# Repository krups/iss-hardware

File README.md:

# Kentucky RE-entry Probe Experiment 2
Board files, schematics, DXF, BOM, partslist and documentation for the KREPE-2 mission, part of the KRUPS campaign at the University of Kentucky. Documentation PDF can be found [Flight Computer Hardware Manual](doc/krepe-flight-computer-manual.pdf).

Documentation for the KREPE-1 mission can be found on the krepe1 branch [here](https://github.com/krups/iss-hardware/blob/krepe1/doc/krepe-flight-computer-manual.pdf).

### Board renders

### Libraries and datasheets for components
- Thermocouple to digital converter
  -  [MAX31856 Library](https://github.com/adafruit/Adafruit_MAX31856)
  -  [MAX31856 Datasheet](https://datasheets.maximintegrated.com/en/ds/MAX31856.pdf)
- Analog Multiplexer
  - [ADG609BRUZ datasheet](https://www.analog.com/media/en/technical-documentation/data-sheets/ADG608_609.pdf)
- Debug Radio
  - [RFM69HCW](https://www.digikey.com/product-detail/en/sparkfun-electronics/COM-13909/1568-1394-ND/6023504)
- 9-axis IMU
  - [DPE Library](https://github.com/drcpattison/DPEng_ICM20948_AK09916)
  - [Sparkfun Library](https://github.com/sparkfun/SparkFun_ICM-20948_ArduinoLibrary)
  - [Datasheet](https://www.invensense.com/wp-content/uploads/2016/06/DS-000189-ICM-20948-v1.3.pdf)
- Solid state relay
  - [Datasheet](https://www.digikey.com/product-detail/en/panasonic-electric-works/AQV252GAX/255-3375-1-ND/2810282)
- High G Accelerometer
  - [Datasheet](https://www.digikey.com/product-detail/en/analog-devices-inc/ADXL377BCPZ-RL7/ADXL377BCPZ-RL7CT-ND/3678489)
- Safety Co-processor
  - [Datasheet](https://www.digikey.com/product-detail/en/microchip-technology/ATSAMD21E16B-MFT/ATSAMD21E16B-MFTCT-ND/5455793)
  - [Arduino variant reference](https://github.com/adafruit/ArduinoCore-samd/blob/master/variants/trinket_m0/variant.cpp)
 
### Teensy pin assignments wrt. to Arduino 

| Teensy Arduino Pin      | Net Name                 | Notes      |
|-------------------------|--------------------------|------------------|
| 0                       | CAPSENSE 1               |  input, read with ```touchRead(pin)```                |
| 1                       | CAPSENSE 0               |  input, read with ```touchRead(pin)```                |
| 3                       | LED IRIDIUM ON           |  active high                |
| 4                       | LED IRIDIUM SIGNAL_OK    |    active high              |
| 5                       | LED IRIDIUM TRANSMITTING |    active high              |
| 6                       | LED ISM TRANSMITTING     |    active high              |
| 7                       | LED ACTIVITY             |    active high              |
| 8			  | CS_DSP		     | active low chip select for DSP310 pressure sensor |
| 9                       | CS_ISM                   |    rfm69 chip select              |
| 11                      | MOSI                     |                  |
| 12                      | MISO                     |                  |
| 13                      | SCLK                     |                  |
| 14                      | BAT_STAT                 |    high when charging              |
| 15                      | CAPSENSE2                |     input, read with ```touchRead(pin)```             |
| 16                      | MUX0                     |    output to analog mux              |
| 17                      | MUX1                     |    output to analog mux              |
| 18                      | SDA                      |                  |
| 19                      | SCL                      |                  |
| 20                      | CS@TC1                   |  U12 chip select                |
| 21                      | CS@TC2                   |  U13 chip select                |
| A8                      | BAT SENSE                | (A8)  halved by voltage divider           |
| 23                      | PRI ACT                  | output to iridium activation 'AND' gate  |
| 24                      | BUZZER                   |     buzzer output             |
| 25                      | TC1 FAULT                | (ACTIVE LOW)     |
| 26                      | TC2 FAULT                | (ACTIVE LOW)     |
| 27                      | SEC CTRL 2               |       i/o to safety processor           |
| 28                      | RESET ISM                |  reset to rfm69                |
| 28                      | INT ISM                  |  interrupt from rfm69                |
| 30                      | CAPSENSE3                |  input, read with ```touchRead(pin)```                |
| 31                      | RIRI                     | (IRIDIUM OUTPUT) |
| 32                      | TIRI                     | (IRIDIUM INPUT)  |
| 33                      | RADIO OFF SIG            | pulled high when 3.3v to ism radio is present                 |
| 34                      | FSYNC                    | IMU sync signal (not necessary for functionality)            |
| 35                      | INT                      | IMU interrupt pin (not necessary for functionality)            |
| 36                      | XOUT                     | (A17)  high g accel output          |
| 37                      | YOUT                     | (A18)  high g accel output          |
| 38                      | ZOUT                     | (A19)  high g accel output          |
| 39                      | SEC CTRL 1               |   i/o to safety processor               |
| A21                     | IRIDIUM TX ACT           |     iridium output indicating the module is actively transmitting RF             |
| A22                     | IRIDIUM STATUS           |  iridium output indicating an SBD message has arrived                |

### Safety processor pin assignments wrt. to Arduino 

The last four pins for the safety processor will need to be added into the board variant file for the trinket m0 since only 5 pins are mapped to physical pads on the current m0 variant.cpp file (or we can make our own arduino board support package ;) )

```SEC CTRL 1``` and ```SEC CTRL 1``` are to be used to coordinate use of the SPI bus so that both the Teensy and safety processor do not drive bus lines to opposite logic levels.

| Safety Processor Arduino Pin|   Net Name                       |                 Note |
|-------------------------|--------------------------|------------------|
| 1                       | CS@TC1                   |    also connected to teensy GPIO              |
| 13                      | CS@TC2                   |    also connected to teensy GPIO              |
| 7                       | SEC ACT                  |     output to activation 'AND' gate             |
| 8                       | SEC CTRL 1               |  i/o with teensy                |
| 0                       | SEC CTRL 2               |  i/o with teensy                |
| PA14                    | TC1 FAULT                |         input        |
| PA15                    | TC2 FAULT                |    input            |
| PA17                    | MUX0                     |       need to use i/o with teensy to avoid collisions on SPI bus           |
| PA18                    | MUX1                     |        need to use i/o with teensy to avoid collisions on SPI bus         |

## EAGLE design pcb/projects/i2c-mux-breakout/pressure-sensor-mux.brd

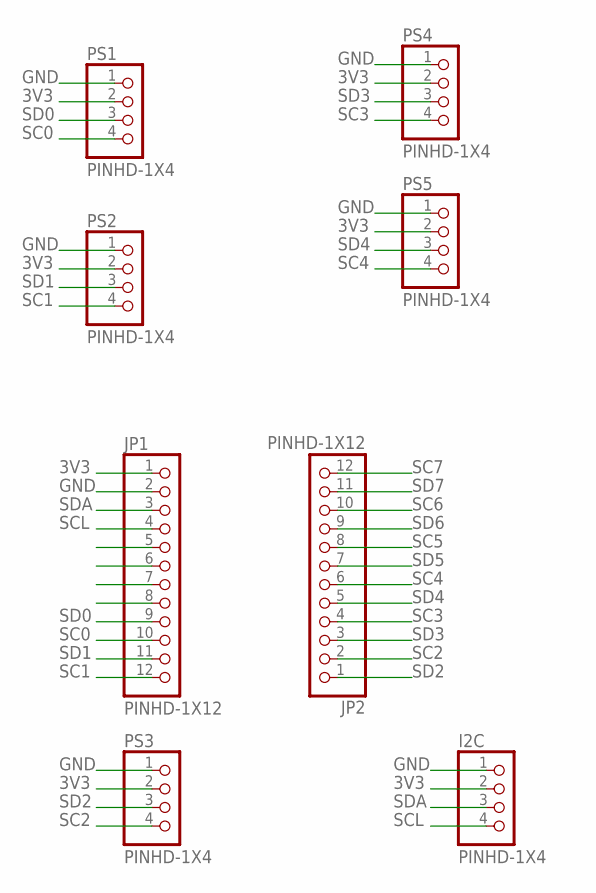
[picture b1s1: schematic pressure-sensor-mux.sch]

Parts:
I2C: PINHD-1X4; 1X04
JP1, JP2: PINHD-1X12; 1X12
PS1, PS2, PS3, PS4, PS5: PINHD-1X4; 1X04

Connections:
3V3: I2C.2, JP1.1, PS1.2, PS2.2, PS3.2, PS4.2, PS5.2
GND: I2C.1, JP1.2, PS1.1, PS2.1, PS3.1, PS4.1, PS5.1
SC0: JP1.10, PS1.4
SC1: JP1.12, PS2.4
SC2: JP2.2, PS3.4
SC3: JP2.4, PS4.4
SC4: JP2.6, PS5.4
SC5: JP2.8
SC6: JP2.10
SC7: JP2.12
SCL: I2C.4, JP1.4
SD0: JP1.9, PS1.3
SD1: JP1.11, PS2.3
SD2: JP2.1, PS3.3
SD3: JP2.3, PS4.3
SD4: JP2.5, PS5.3
SD5: JP2.7
SD6: JP2.9
SD7: JP2.11
SDA: I2C.3, JP1.3

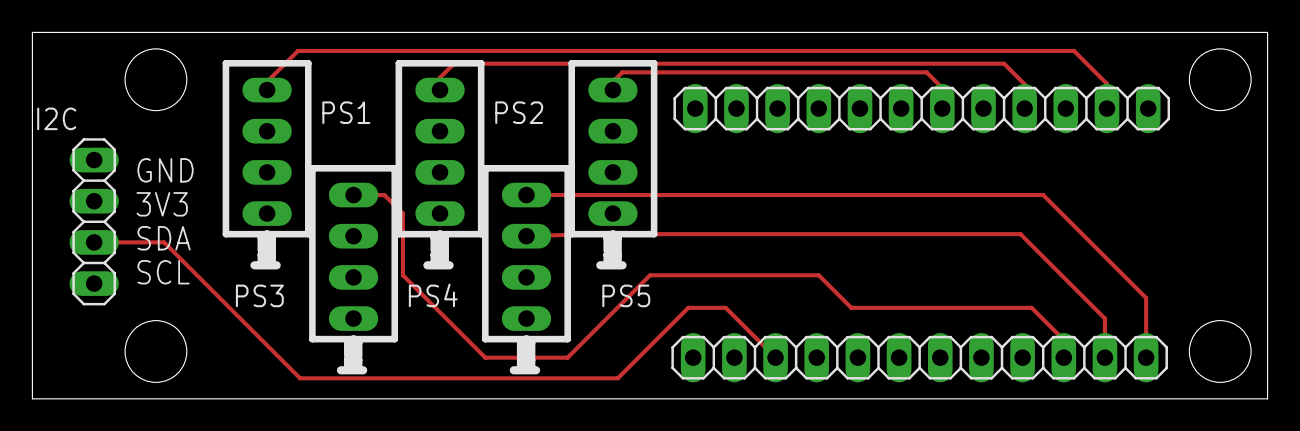
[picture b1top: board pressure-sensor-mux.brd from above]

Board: 4 copper layers, 76.2 x 22.6 mm, 8 parts (0 on the bottom side), 14 nets.

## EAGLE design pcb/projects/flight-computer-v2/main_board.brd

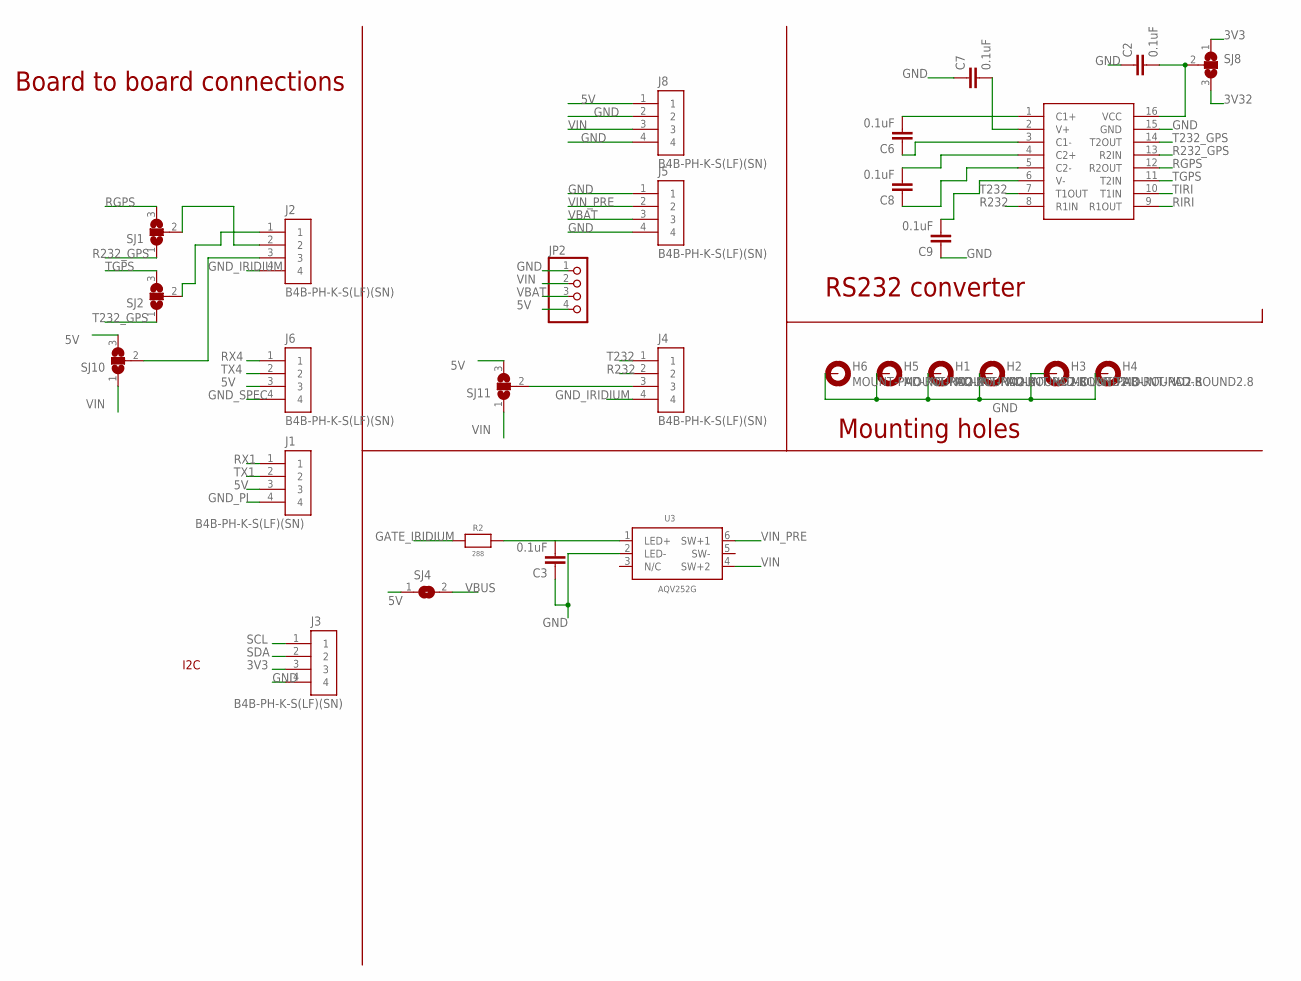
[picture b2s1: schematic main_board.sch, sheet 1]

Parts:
C2, C3, C6, C7, C8, C9: 0.1uF; C0603
H1, H2, H3, H4, H5, H6: MOUNT-PAD-ROUND2.8; 2,8-PAD
J1, J2, J3, J4, J5, J6, J8: B4B-PH-K-S(LF)(SN); JST_B4B-PH-K-S(LF)(SN)
JP2: PINHD-1X4; 1X04
R2: 288; 0603-NO
SJ1, SJ2, SJ8, SJ10, SJ11: SJ2W; SJ_2
SJ4: SJ
U3: AQV252G; SOP6
U11: UM3232EEAE; RQ_16_ADI

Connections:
3V3: J3.3, SJ8.1; also elsewhere on the board
3V32: SJ8.3; also elsewhere on the board
5V: J1.3, J6.3, J8.1, JP2.4, SJ4.1, SJ10.3, SJ11.3; also elsewhere on the board
GATE_IRIDIUM: R2.1; also elsewhere on the board
GND: C2.1, C3.1, C7.1, C9.1, H1.B2,8, H2.B2,8, H3.B2,8, H4.B2,8, H5.B2,8, H6.B2,8, J3.4, J5.1, J5.4, J8.2, J8.4, JP2.1, U3.2 (LED-), U11.15 (GND); also elsewhere on the board
GND_IRIDIUM: J2.4, J4.4
GND_PI: J1.4
GND_SPEC: J6.4
unnamed: J2.1, SJ2.2
unnamed: J2.2, SJ1.2
unnamed: C6.2, U11.1 (C1+)
unnamed: J2.3, SJ10.2
unnamed: C2.2, SJ8.2, U11.16 (VCC)
unnamed: C7.2, U11.2 (V+)
unnamed: C6.1, U11.3 (C1-)
unnamed: C8.2, U11.4 (C2+)
unnamed: C8.1, U11.5 (C2-)
unnamed: C9.2, U11.6 (V-)
unnamed: J4.3, SJ11.2
unnamed: C3.2, R2.2, U3.1 (LED+)
R232: J4.2, U11.8 (R1IN)
R232_GPS: SJ1.1, U11.13 (R2IN)
RGPS: SJ1.3, U11.12 (R2OUT); also elsewhere on the board
RIRI: U11.9 (R1OUT); also elsewhere on the board
RX1: J1.1; also elsewhere on the board
RX4: J6.1; also elsewhere on the board
SCL: J3.1; also elsewhere on the board
SDA: J3.2; also elsewhere on the board
T232: J4.1, U11.7 (T1OUT)
T232_GPS: SJ2.1, U11.14 (T2OUT)
TGPS: SJ2.3, U11.11 (T2IN); also elsewhere on the board
TIRI: U11.10 (T1IN); also elsewhere on the board
TX1: J1.2; also elsewhere on the board
TX4: J6.2; also elsewhere on the board
VBAT: J5.3, JP2.3; also elsewhere on the board
VBUS: SJ4.2; also elsewhere on the board
VIN: J8.3, JP2.2, SJ10.1, SJ11.1, U3.4 (SW+2)
VIN_PRE: J5.2, U3.6 (SW+1)

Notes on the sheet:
Board to board connections
I2C
RS232 converter
Mounting holes

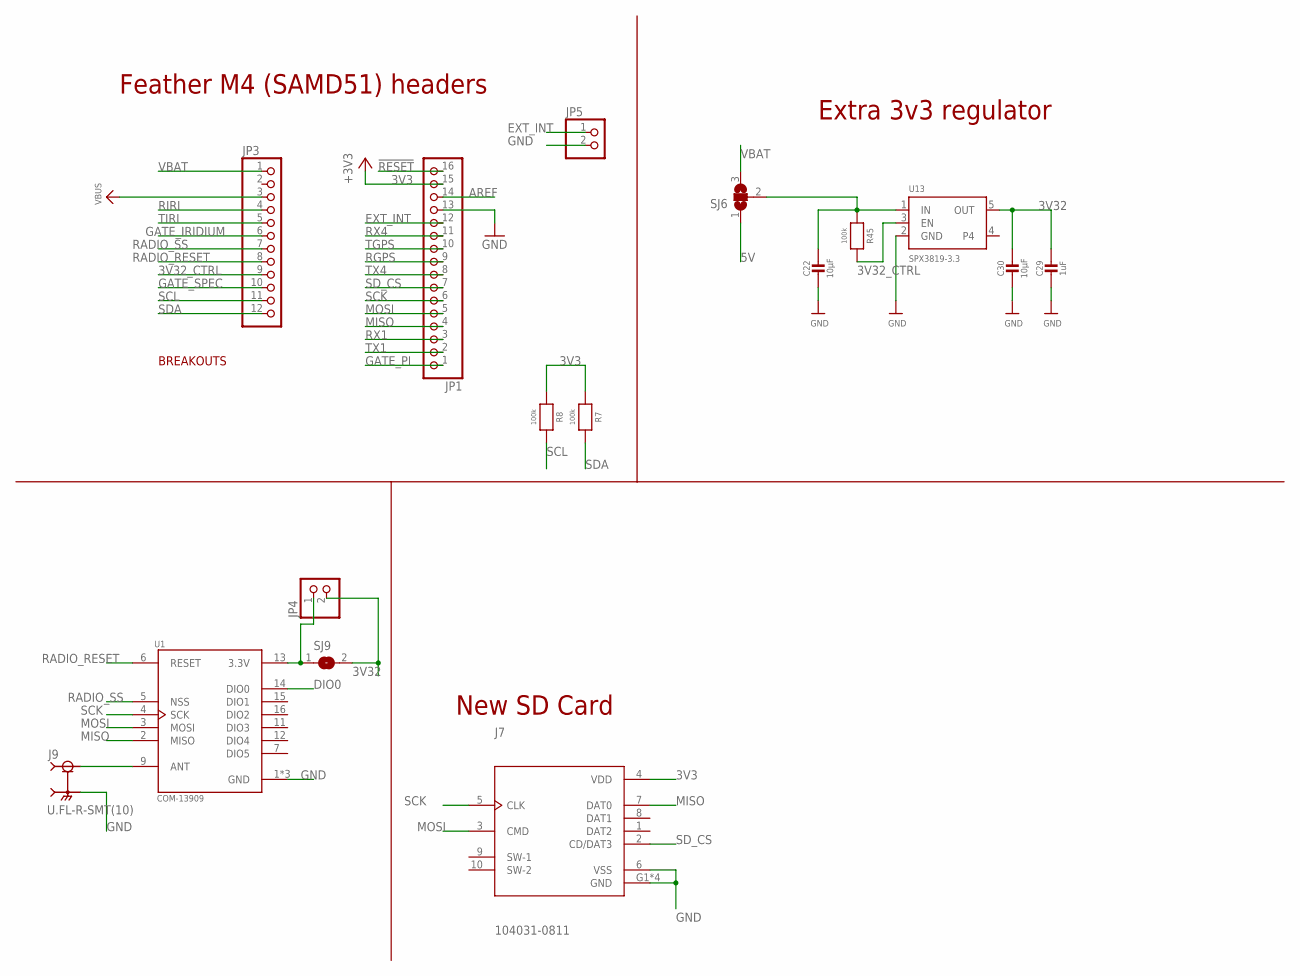
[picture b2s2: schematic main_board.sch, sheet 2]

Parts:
C22, C30: 10µF; 0805-NO
C29: 1uF; 0603-NO
J7: 104031-0811; MOLEX_104031-0811
J9: U.FL-R-SMT(10); HRS_U.FL-R-SMT(10)
JP1: HEADER-1X16ROUND; 1X16_ROUND
JP3: HEADER-1X12; 1X12_ROUND
JP4, JP5: PINHD-1X2; 1X02
R7, R8, R45: 100k; 0603-NO
SJ6: SJ2W; SJ_2
SJ9: SJ
U1: COM-13909; MOD_COM-13909
U13: SPX3819-3.3; SOT23-5

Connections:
3V3: J7.4 (VDD), JP1.15, R7.1, R8.1; also elsewhere on the board
3V32: C29.1, C30.1, JP4.2, SJ9.2, U13.5 (OUT); also elsewhere on the board
3V32_CTRL: JP3.9, R45.2, U13.3 (EN); also elsewhere on the board
5V: SJ6.1; also elsewhere on the board
!RESET: JP1.16
AREF: JP1.14
DIO0: U1.14 (DIO0)
EXT_INT: JP1.12, JP5.1
GATE_IRIDIUM: JP3.6; also elsewhere on the board
GATE_PI: JP1.1; also elsewhere on the board
GATE_SPEC: JP3.10; also elsewhere on the board
GND: C22.2, C29.2, C30.2, J7.6 (VSS), J7.G1 (GND), J7.G2 (GND), J7.G3 (GND), J7.G4 (GND), J9.2 (GND), J9.3 (GND), JP1.13, JP5.2, U1.1 (GND), U1.8 (GND), U1.10 (GND), U13.2 (GND); also elsewhere on the board
MISO: J7.7 (DAT0), JP1.4, U1.2 (MISO)
MOSI: J7.3 (CMD), JP1.5, U1.3 (MOSI)
unnamed: JP4.1, SJ9.1, U1.13 (3.3V)
unnamed: C22.1, R45.1, SJ6.2, U13.1 (IN)
unnamed: J9.1 (SIG), U1.9 (ANT)
RADIO_RESET: JP3.8, U1.6 (RESET)
RADIO_SS: JP3.7, U1.5 (NSS)
RGPS: JP1.9; also elsewhere on the board
RIRI: JP3.4; also elsewhere on the board
RX1: JP1.3; also elsewhere on the board
RX4: JP1.11; also elsewhere on the board
SCK: J7.5 (CLK), JP1.6, U1.4 (SCK)
SCL: JP3.11, R8.2; also elsewhere on the board
SDA: JP3.12, R7.2; also elsewhere on the board
SD_CS: J7.2 (CD/DAT3), JP1.7
TGPS: JP1.10; also elsewhere on the board
TIRI: JP3.5; also elsewhere on the board
TX1: JP1.2; also elsewhere on the board
TX4: JP1.8; also elsewhere on the board
VBAT: JP3.1, SJ6.3; also elsewhere on the board
VBUS: JP3.3; also elsewhere on the board

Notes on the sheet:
BREAKOUTS
Feather M4 (SAMD51) headers
Extra 3v3 regulator
New SD Card

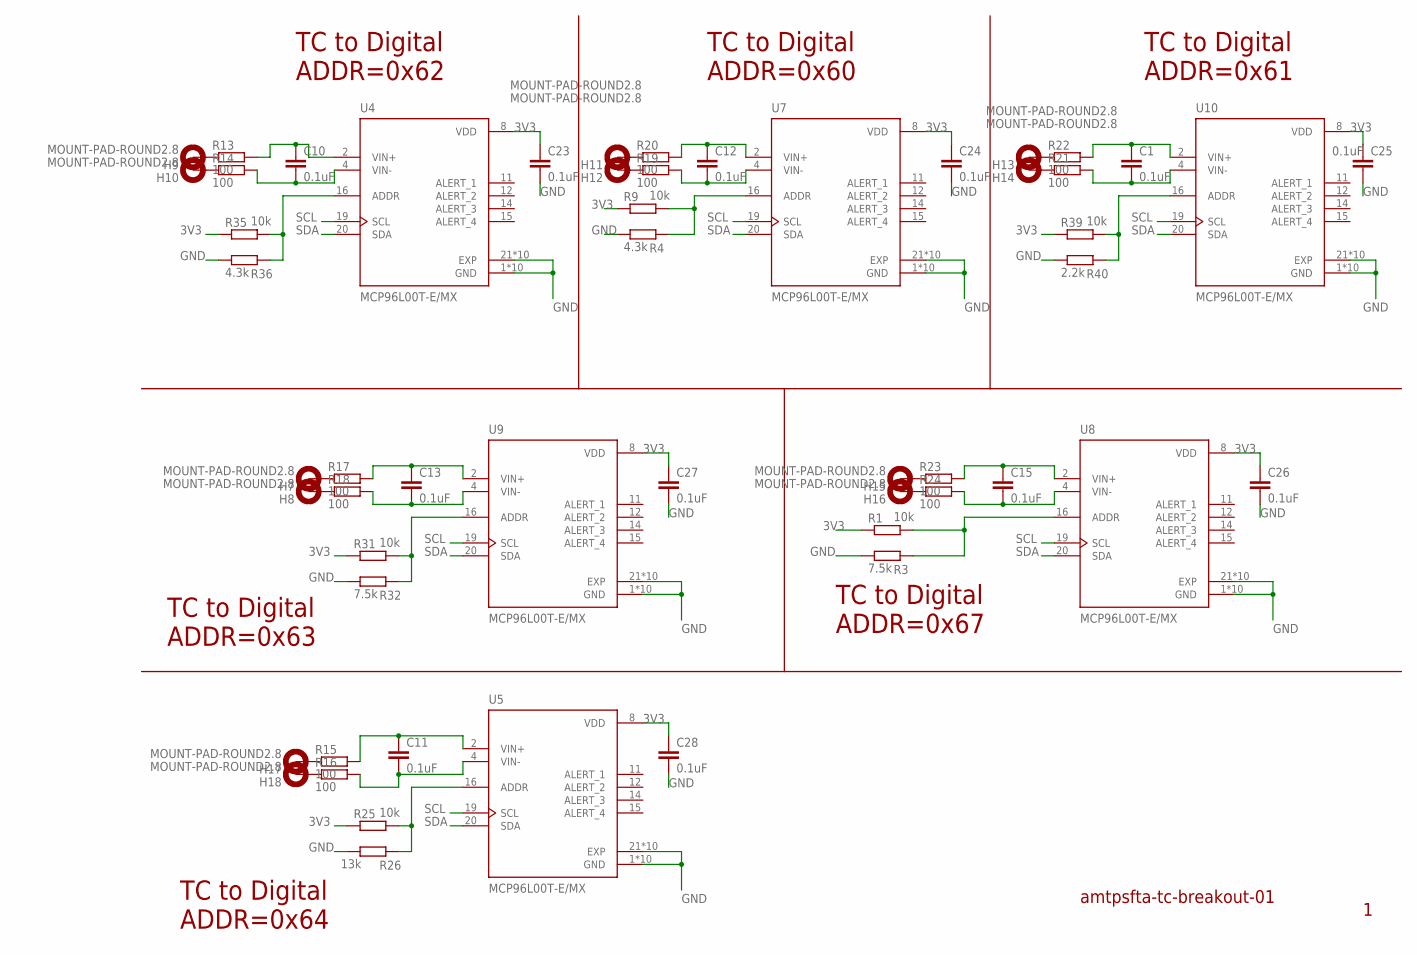
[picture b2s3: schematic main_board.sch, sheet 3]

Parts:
C1, C10, C11, C12, C13, C15, C23, C24, C25, C26, C27, C28: 0.1uF; C0603
H7, H8, H9, H10, H11, H12, H13, H14, H15, H16, H17, H18: MOUNT-PAD-ROUND2.8; 2,8-PAD
R1, R9, R25, R31, R35, R39: 10k; R0603
R3, R32: 7.5k; R0603
R4, R36: 4.3k; R0603
R13, R14, R15, R16, R17, R18, R19, R20, R21, R22, R23, R24: 100; R0603
R26: 13k; R0603
R40: 2.2k; R0603
U4, U5, U7, U8, U9, U10: MCP96L00T-E/MX; QFN65P500X500X100-21N_MCP96L00T-E/MX

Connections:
3V3: C23.1, C24.1, C25.1, C26.1, C27.1, C28.1, R1.1, R9.1, R25.1, R31.1, R35.1, R39.1, U4.8 (VDD), U5.8 (VDD), U7.8 (VDD), U8.8 (VDD), U9.8 (VDD), U10.8 (VDD); also elsewhere on the board
GND: C23.2, C24.2, C25.2, C26.2, C27.2, C28.2, R3.1, R4.1, R26.1, R32.1, R36.1, R40.1, U4.1 (GND), U4.3 (GND), U4.5 (GND), U4.6 (GND), U4.7 (GND), U4.9 (GND), U4.10 (GND), U4.13 (GND), U4.17 (GND), U4.18 (GND), U4.21 (EXP), U4.22 (EXP), U4.23 (EXP), U4.24 (EXP), U4.25 (EXP), U4.26 (EXP), U4.27 (EXP), U4.28 (EXP), U4.29 (EXP), U4.30 (EXP), U5.1 (GND), U5.3 (GND), U5.5 (GND), U5.6 (GND), U5.7 (GND), U5.9 (GND), U5.10 (GND), U5.13 (GND), U5.17 (GND), U5.18 (GND), U5.21 (EXP), U5.22 (EXP), U5.23 (EXP), U5.24 (EXP), U5.25 (EXP), U5.26 (EXP), U5.27 (EXP), U5.28 (EXP), U5.29 (EXP), U5.30 (EXP), U7.1 (GND), U7.3 (GND), U7.5 (GND), U7.6 (GND), U7.7 (GND), U7.9 (GND), U7.10 (GND), U7.13 (GND), U7.17 (GND), U7.18 (GND), U7.21 (EXP), U7.22 (EXP), U7.23 (EXP), U7.24 (EXP), U7.25 (EXP), U7.26 (EXP), U7.27 (EXP), U7.28 (EXP), U7.29 (EXP), U7.30 (EXP), U8.1 (GND), U8.3 (GND), U8.5 (GND), U8.6 (GND), U8.7 (GND), U8.9 (GND), U8.10 (GND), U8.13 (GND), U8.17 (GND), U8.18 (GND), U8.21 (EXP), U8.22 (EXP), U8.23 (EXP), U8.24 (EXP), U8.25 (EXP), U8.26 (EXP), U8.27 (EXP), U8.28 (EXP), U8.29 (EXP), U8.30 (EXP), U9.1 (GND), U9.3 (GND), U9.5 (GND), U9.6 (GND), U9.7 (GND), U9.9 (GND), U9.10 (GND), U9.13 (GND), U9.17 (GND), U9.18 (GND), U9.21 (EXP), U9.22 (EXP), U9.23 (EXP), U9.24 (EXP), U9.25 (EXP), U9.26 (EXP), U9.27 (EXP), U9.28 (EXP), U9.29 (EXP), U9.30 (EXP), U10.1 (GND), U10.3 (GND), U10.5 (GND), U10.6 (GND), U10.7 (GND), U10.9 (GND), U10.10 (GND), U10.13 (GND), U10.17 (GND), U10.18 (GND), U10.21 (EXP), U10.22 (EXP), U10.23 (EXP), U10.24 (EXP), U10.25 (EXP), U10.26 (EXP), U10.27 (EXP), U10.28 (EXP), U10.29 (EXP), U10.30 (EXP); also elsewhere on the board
unnamed: H7.B2,8, R17.1
unnamed: H8.B2,8, R18.1
unnamed: R1.2, R3.2, U8.16 (ADDR)
unnamed: R4.2, R9.2, U7.16 (ADDR)
unnamed: H9.B2,8, R13.1
unnamed: H10.B2,8, R14.1
unnamed: H11.B2,8, R20.1
unnamed: H12.B2,8, R19.1
unnamed: H13.B2,8, R22.1
unnamed: H14.B2,8, R21.1
unnamed: H15.B2,8, R23.1
unnamed: H16.B2,8, R24.1
unnamed: H17.B2,8, R15.1
unnamed: H18.B2,8, R16.1
unnamed: C10.1, R13.2, U4.2 (VIN+)
unnamed: C10.2, R14.2, U4.4 (VIN-)
unnamed: C12.1, R20.2, U7.2 (VIN+)
unnamed: C12.2, R19.2, U7.4 (VIN-)
unnamed: C15.1, R23.2, U8.2 (VIN+)
unnamed: C1.2, R21.2, U10.4 (VIN-)
unnamed: C15.2, R24.2, U8.4 (VIN-)
unnamed: C1.1, R22.2, U10.2 (VIN+)
unnamed: C13.1, R17.2, U9.2 (VIN+)
unnamed: C13.2, R18.2, U9.4 (VIN-)
unnamed: C11.1, R15.2, U5.2 (VIN+)
unnamed: C11.2, R16.2, U5.4 (VIN-)
unnamed: R25.2, R26.2, U5.16 (ADDR)
unnamed: R31.2, R32.2, U9.16 (ADDR)
unnamed: R35.2, R36.2, U4.16 (ADDR)
unnamed: R39.2, R40.2, U10.16 (ADDR)
SCL: U4.19 (SCL), U5.19 (SCL), U7.19 (SCL), U8.19 (SCL), U9.19 (SCL), U10.19 (SCL); also elsewhere on the board
SDA: U4.20 (SDA), U5.20 (SDA), U7.20 (SDA), U8.20 (SDA), U9.20 (SDA), U10.20 (SDA); also elsewhere on the board

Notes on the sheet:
TC to Digital ADDR=0x60
TC to Digital ADDR=0x61
TC to Digital ADDR=0x62
TC to Digital ADDR=0x67
TC to Digital ADDR=0x63
TC to Digital ADDR=0x64
amtpsfta-tc-breakout-01

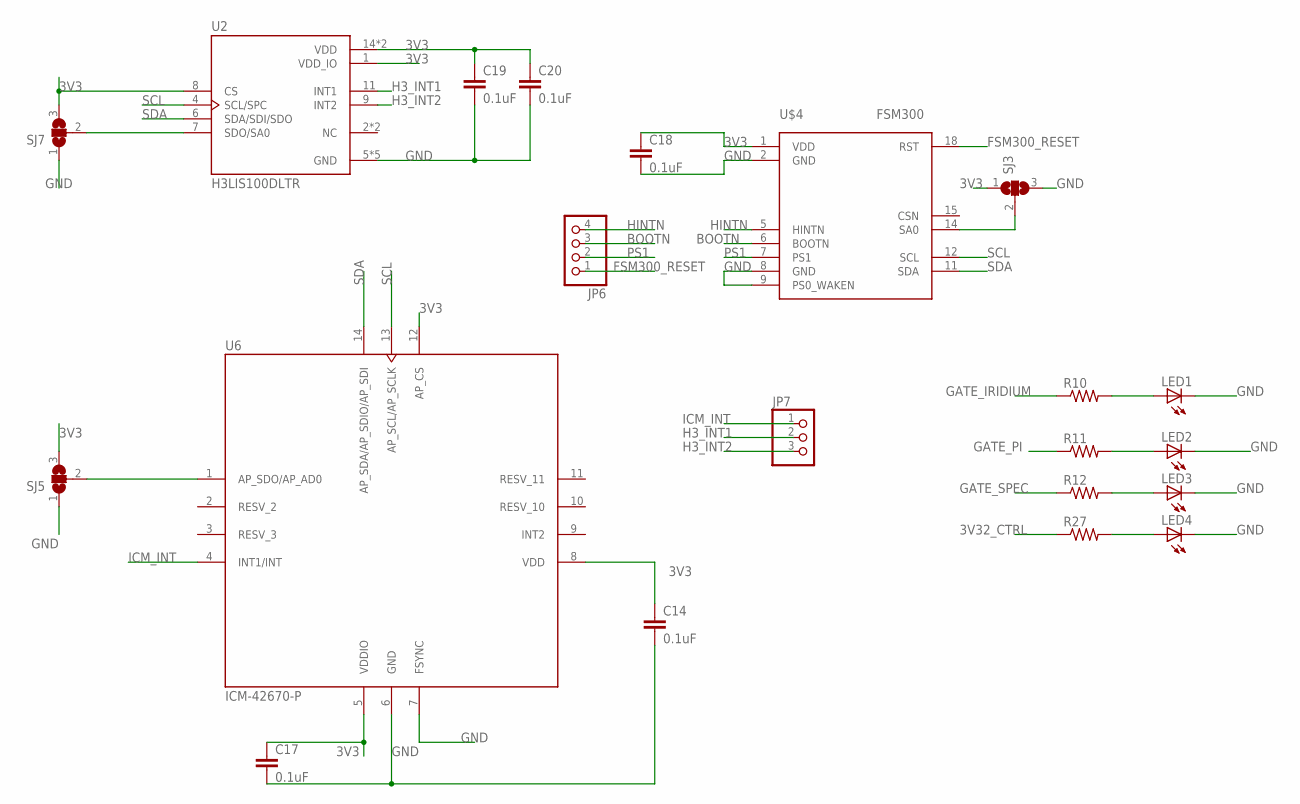
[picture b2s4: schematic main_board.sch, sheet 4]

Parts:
C14, C17, C18, C19, C20: 0.1uF; C0603
JP6: PINHD-1X4; 1X04
JP7: PINHD-1X3; 1X03
LED1, LED2, LED3, LED4: LEDCHIPLED_0603; CHIPLED_0603
R10, R11, R12, R27: R-US_R0603; R0603
SJ3, SJ5, SJ7: SJ2W; SJ_2
U2: H3LIS100DLTR; PQFN50P300X300X100-16N
U6: ICM-42670-P; IC_ICM-42670-P
U$4: FSM300; FSM300_FOOTPRINT

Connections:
3V3: C14.1, C17.1, C18.1, C19.1, C20.1, SJ3.1, SJ5.3, SJ7.3, U2.1 (VDD_IO), U2.8 (CS), U2.14 (VDD), U2.15 (VDD), U6.5 (VDDIO), U6.8 (VDD), U6.12 (AP_CS), U$4.1 (VDD); also elsewhere on the board
3V32_CTRL: R27.1; also elsewhere on the board
BOOTN: JP6.3, U$4.6 (BOOTN)
FSM300_RESET: JP6.1, U$4.18 (RST)
GATE_IRIDIUM: R10.1; also elsewhere on the board
GATE_PI: R11.1; also elsewhere on the board
GATE_SPEC: R12.1; also elsewhere on the board
GND: C14.2, C17.2, C18.2, C19.2, C20.2, LED1.C, LED2.C, LED3.C, LED4.C, SJ3.3, SJ5.1, SJ7.1, U2.5 (GND), U2.10 (GND), U2.12 (GND), U2.13 (GND), U2.16 (GND), U6.6 (GND), U6.7 (FSYNC), U$4.2 (GND), U$4.8 (GND), U$4.9 (PS0_WAKEN); also elsewhere on the board
H3_INT1: JP7.2, U2.11 (INT1)
H3_INT2: JP7.3, U2.9 (INT2)
HINTN: JP6.4, U$4.5 (HINTN)
ICM_INT: JP7.1, U6.4 (INT1/INT)
unnamed: SJ5.2, U6.1 (AP_SDO/AP_AD0)
unnamed: LED1.A, R10.2
unnamed: LED2.A, R11.2
unnamed: SJ7.2, U2.7 (SDO/SA0)
unnamed: LED3.A, R12.2
unnamed: LED4.A, R27.2
unnamed: SJ3.2, U$4.14 (SA0)
PS1: JP6.2, U$4.7 (PS1)
SCL: U2.4 (SCL/SPC), U6.13 (AP_SCL/AP_SCLK), U$4.12 (SCL); also elsewhere on the board
SDA: U2.6 (SDA/SDI/SDO), U6.14 (AP_SDA/AP_SDIO/AP_SDI), U$4.11 (SDA); also elsewhere on the board

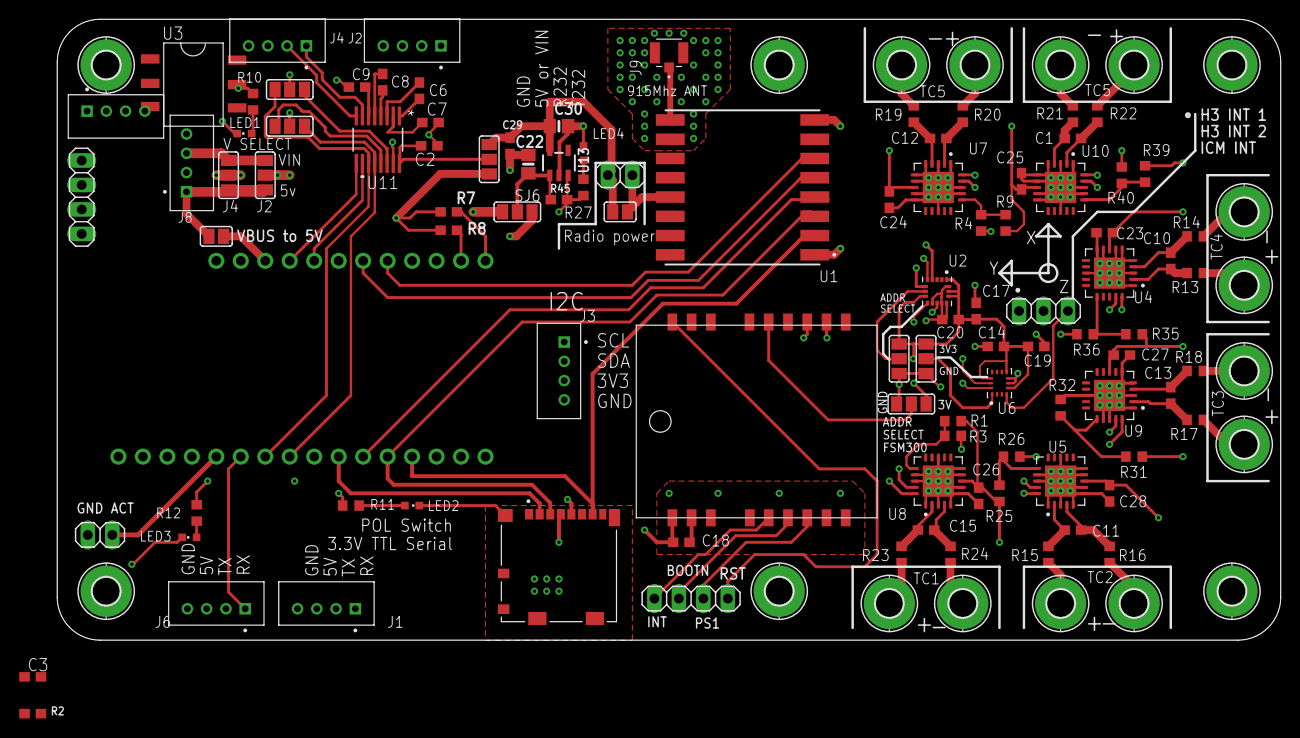
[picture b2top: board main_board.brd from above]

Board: 4 copper layers, 127.0 x 64.4 mm, 120 parts (0 on the bottom side), 93 nets.

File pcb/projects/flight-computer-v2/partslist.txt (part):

Partlist

Exported from main_board.brd at 11/17/22 8:33 PM

EAGLE Version 9.6.2 Copyright (c) 1988-2020 Autodesk, Inc.

Assembly variant: 

Part     Value              Package                              Library            Position (mil)        Orientation

C1       0.1uF              C0603                                rcl                (4150 2050)           R180
C2       0.1uF              C0603                                rcl                (1450 2020)           R180
C6       0.1uF              C0603                                rcl                (1400 2250)           R270
C7       0.1uF              C0603                                rcl                (1450 2110)           R180
C8       0.1uF              C0603                                rcl                (1265 2270)           R270
C9       0.1uF              C0603                                rcl                (1155 2255)           R0
C10      0.1uF              C0603                                rcl                (4550 1550)           R90
C11      0.1uF              C0603                                rcl                (4150 450)            R0
C12      0.1uF              C0603                                rcl                (3600 2050)           R180
C13      0.1uF              C0603                                rcl                (4550 1000)           R90
C14      0.1uF              C0603                                rcl                (3835 1200)           R180
C15      0.1uF              C0603                                rcl                (3550 450)            R0
C17      0.1uF              C0603                                rcl                (3755 1345)           R90
C18      0.1uF              C0603                                rcl                (2550 400)            R0
C19      0.1uF              C0603                                rcl                (4000 1200)           R0
C20      0.1uF              C0603                                rcl                (3650 1310)           R180
C22      10µF               0805-NO                              microbuilder       (1850 1950)           R90
C23      0.1uF              C0603                                rcl                (4280 1665)           R180
C24      0.1uF              C0603                                rcl                (3400 1800)           R270
C25      0.1uF              C0603                                rcl                (3940 1875)           R90
C26      0.1uF              C0603                                rcl                (3765 590)            R270
C27      0.1uF              C0603                                rcl                (4350 1165)           R0
C28      0.1uF              C0603                                rcl                (4300 600)            R270
C29      1uF                0603-NO                              microbuilder       (1750 2000)           R270
C30      10µF               0805-NO                              microbuilder       (2000 2100)           R0
H1       MOUNT-PAD-ROUND2.8 2,8-PAD                              holes              (2950 200)            R0
H2       MOUNT-PAD-ROUND2.8 2,8-PAD                              holes              (2950 2350)           R0
H3       MOUNT-PAD-ROUND2.8 2,8-PAD                              holes              (4800 2350)           R0
H4       MOUNT-PAD-ROUND2.8 2,8-PAD                              holes              (4800 200)            R0
H5       MOUNT-PAD-ROUND2.8 2,8-PAD                              holes              (200 2350)            R0
H6       MOUNT-PAD-ROUND2.8 2,8-PAD                              holes              (200 200)             R0
H7       MOUNT-PAD-ROUND2.8 2,8-PAD                              holes              (4850 800)            R0
H8       MOUNT-PAD-ROUND2.8 2,8-PAD                              holes              (4850 1100)           R0
H9       MOUNT-PAD-ROUND2.8 2,8-PAD                              holes              (4850 1450)           R0
H10      MOUNT-PAD-ROUND2.8 2,8-PAD                              holes              (4850 1750)           R0
H11      MOUNT-PAD-ROUND2.8 2,8-PAD                              holes              (3750 2350)           R0
H12      MOUNT-PAD-ROUND2.8 2,8-PAD                              holes              (3450 2350)           R0
H13      MOUNT-PAD-ROUND2.8 2,8-PAD                              holes              (4400 2350)           R0
H14      MOUNT-PAD-ROUND2.8 2,8-PAD                              holes              (4100 2350)           R0
H15      MOUNT-PAD-ROUND2.8 2,8-PAD                              holes              (3400 150)            R0
H16      MOUNT-PAD-ROUND2.8 2,8-PAD                              holes              (3700 150)            R0
H17      MOUNT-PAD-ROUND2.8 2,8-PAD                              holes              (4100 150)            R0
H18      MOUNT-PAD-ROUND2.8 2,8-PAD                              holes              (4400 150)            R0
J1       B4B-PH-K-S(LF)(SN) JST_B4B-PH-K-S(LF)(SN)               B4B-PH-K-S_LF__SN_ (1100 150)            R0
J2       B4B-PH-K-S(LF)(SN) JST_B4B-PH-K-S(LF)(SN)               B4B-PH-K-S_LF__SN_ (1450 2450)           R0
J3       B4B-PH-K-S(LF)(SN) JST_B4B-PH-K-S(LF)(SN)               B4B-PH-K-S_LF__SN_ (2050 1100)           R90
J4       B4B-PH-K-S(LF)(SN) JST_B4B-PH-K-S(LF)(SN)               B4B-PH-K-S_LF__SN_ (900 2450)            R0
J5       B4B-PH-K-S(LF)(SN) JST_B4B-PH-K-S(LF)(SN)               B4B-PH-K-S_LF__SN_ (290 1810)            R90
J6       B4B-PH-K-S(LF)(SN) JST_B4B-PH-K-S(LF)(SN)               B4B-PH-K-S_LF__SN_ (650 150)             R0
J7       104031-0811        MOLEX_104031-0811                    104031-0811        (2050 300)            R180
J8       B4B-PH-K-S(LF)(SN) JST_B4B-PH-K-S(LF)(SN)               B4B-PH-K-S_LF__SN_ (550 1950)            R270
J9       U.FL-R-SMT(10)     HRS_U.FL-R-SMT(10)                   U.FL-R-SMT_10_     (2500 2400)           R90
JP1                         1X16_ROUND                           microbuilder       (1000 750)            R180
JP2                         1X04                                 pinhead            (115 1810)            R270
JP3                         1X12_ROUND                           microbuilder       (1200 1550)           R0
JP4                         1X02                                 pinhead            (2300 1900)           R180
JP5                         1X02                                 pinhead            (175 430)             R180
JP6                         1X04                                 pinhead            (2590 170)            R180
JP7                         1X03                                 pinhead            (4030 1345)           R180
LED1                        CHIPLED_0603                         adafruit           (765 2070)            R90
LED2                        CHIPLED_0603                         adafruit           (1450 550)            R270
LED3                        CHIPLED_0603                         adafruit           (540 420)             R90
LED4                        CHIPLED_0603                         adafruit           (2150 1990)           R0
R1       10k                R0603                                rcl                (3660 895)            R180
R2       100k               0603-NO                              microbuilder       (685 2220)            R270
R3       7.5k               R0603                                rcl                (3660 835)            R180
R4       4.3k               R0603                                rcl                (3775 1705)           R90
R5       100k               0603-NO                              microbuilder       (1050 600)            R0
R6       100k               0603-NO                              microbuilder       (800 600)             R180
R7       100k               0603-NO                              microbuilder       (1550 1750)           R0
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
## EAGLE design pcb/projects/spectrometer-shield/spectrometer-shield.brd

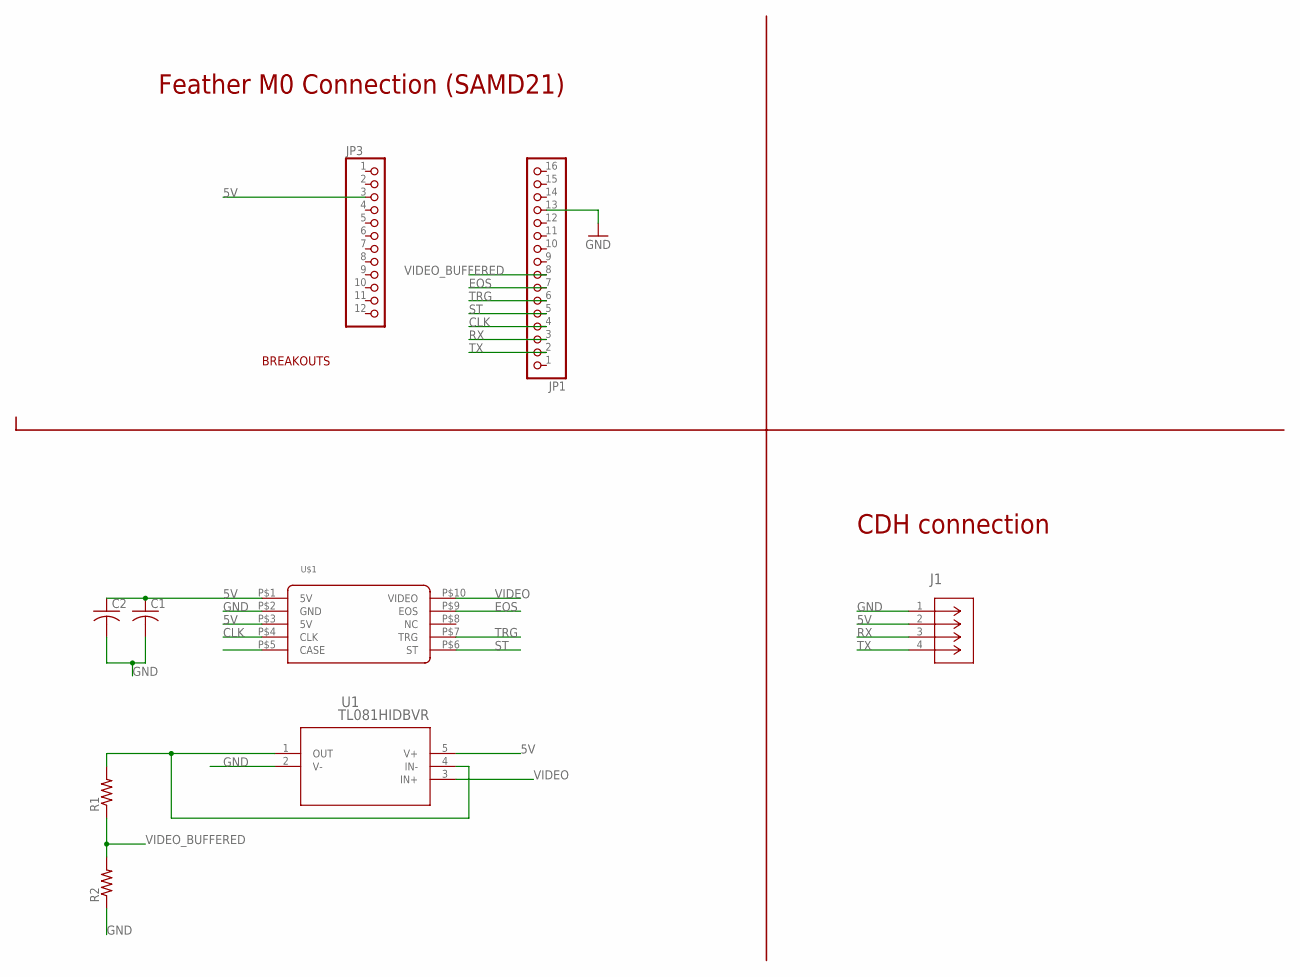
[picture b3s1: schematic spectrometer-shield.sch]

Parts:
C1: C-USC1206; C1206
C2: C-USC0603; C0603
J1: S4B-PH-SM4-TB(LF)(SN); CONN_S4B-PH-SM4-TB(LF)(SN)_JST
JP1: HEADER-1X16ROUND; 1X16_ROUND
JP3: HEADER-1X12; 1X12_ROUND
R1, R2: R-US_R0603; R0603
U1: TL081HIDBVR; SOT-23-5_DBV_TEX
U$1: C12880MA; C12880MA_FOOTPRINT

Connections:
5V: C1.1, C2.1, J1.2, JP3.3, U1.5 (V+), U$1.P$1 (5V), U$1.P$3 (5V)
CLK: JP1.4, U$1.P$4 (CLK)
EOS: JP1.7, U$1.P$9 (EOS)
GND: C1.2, C2.2, J1.1, JP1.13, R2.1, U1.2 (V-), U$1.P$2 (GND), U$1.P$5 (CASE)
unnamed: R1.2, U1.1 (OUT), U1.4 (IN-)
RX: J1.3, JP1.3
ST: JP1.5, U$1.P$6 (ST)
TRG: JP1.6, U$1.P$7 (TRG)
TX: J1.4, JP1.2
VIDEO: U1.3 (IN+), U$1.P$10 (VIDEO)
VIDEO_BUFFERED: JP1.8, R1.1, R2.2

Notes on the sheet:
BREAKOUTS
CDH connection
Feather M0 Connection (SAMD21)

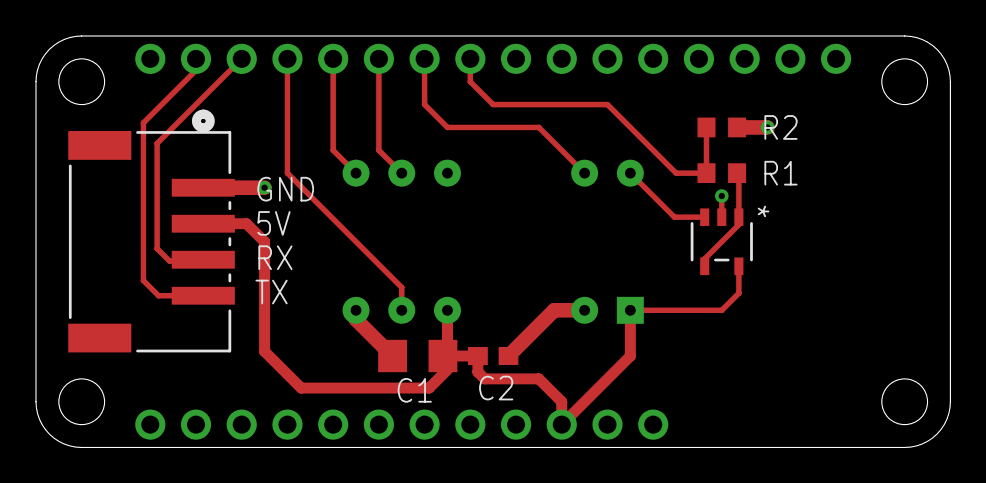
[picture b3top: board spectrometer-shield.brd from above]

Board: 2 copper layers, 50.8 x 22.9 mm, 9 parts (1 on the bottom side), 11 nets.

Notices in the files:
parts and their libraries:
SparkFun-Resistors: Licensing: Creative Commons ShareAlike 4.0 International - https://creativecommons.org/licenses/by-sa/4.0
microbuilder: This work is placed in the public domain, and may be freely used for commercial and non-commercial work with the following conditions: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
